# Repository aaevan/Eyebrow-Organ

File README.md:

# Eyebrow-Organ
A simple instrument you play with combinations of switch presses (0b000 - 0b000) with the left, middle and right eyebrows..

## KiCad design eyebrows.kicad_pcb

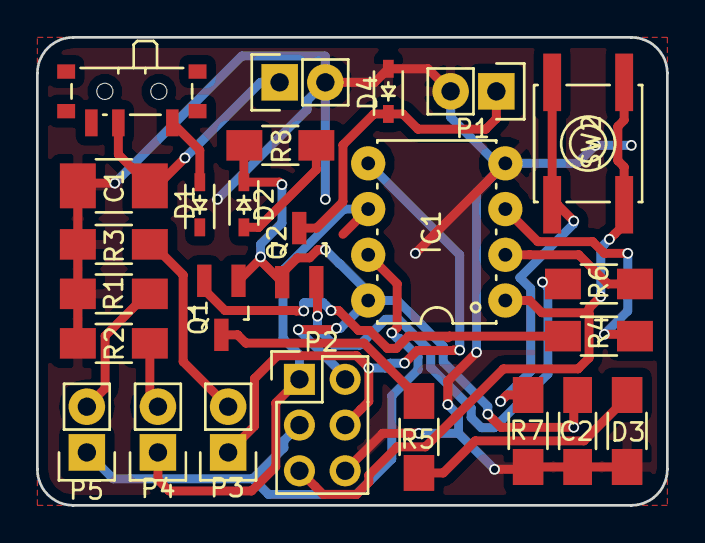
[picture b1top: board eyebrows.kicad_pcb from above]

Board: 2 copper layers, 35.0 x 26.0 mm, 25 parts (0 on the bottom side), 20 nets.

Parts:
C1: 22uF; C_1210_HandSoldering
C2: .1uF; C_1206_HandSoldering
D1, D2: SOD-323_handsoldering
D3: LED; R_1206_HandSoldering
D4: D; SOD-323_handsoldering
IC1: ATTINY85-P; PDIP-8
P1: OUTPUT; Pin_Header_Straight_1x02
P2: PROG; Pin_Header_Straight_2x03
P3: LEFT; Pin_Header_Straight_1x02
P4: MIDDLE; Pin_Header_Straight_1x02
P5: RIGHT; Pin_Header_Straight_1x02
P6: BATTERY; Pin_Header_Straight_1x02
Q1, Q2: SOT-23_Handsoldering
R1, R2, R3, R4, R6, R7: 10k; R_1206_HandSoldering
R5: 125; R_1206_HandSoldering
R8: JMP; R_1206_HandSoldering
SW1: POWER; SW_SPDT_PCM12
SW2: RST; SW_SPST_EVQP0

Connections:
GND: C1.2, C2.2, D3.1, D4.2, IC1.4, P1.2, P2.6, P6.2, R1.2, R2.2, R3.2, R7.1
unnamed: C1.1, P6.1, SW1.2
unnamed: D1.1, D2.2, R8.2
unnamed: D1.2, SW1.1
unnamed: D3.2, R5.2
unnamed: D4.1, P1.1, Q2.3
unnamed: IC1.1, P2.5, SW2.1
unnamed: IC1.2, R6.1
unnamed: IC1.3, R4.1
unnamed: IC1.5, P2.4, P3.1
unnamed: IC1.6, P2.1, P4.1
unnamed: IC1.7, P2.3, P5.1
unnamed: P3.2, R3.1
unnamed: P4.2, R2.1
unnamed: P5.2, R1.1
unnamed: Q1.2, R4.2
unnamed: Q1.3, R5.1
unnamed: Q2.2, R6.2
unnamed: R7.2, SW2.2
VCC: C2.1, D2.1, IC1.8, P2.2, Q1.1, Q2.1, R8.1

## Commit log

2016-01-19 Initialized project.
2016-01-19 Added a render of the board.
2016-01-20 Added generated gerbers and their .zip
